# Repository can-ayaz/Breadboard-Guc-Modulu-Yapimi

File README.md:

# Breadboard-Guc-Modulu-Yapimi
**Breadboard Güç Modülü Yapımı**

Breadbord bildiğimiz üzere çok kullanışlı, ve hemen üzerine devre kompanetlerini geçirerek devre kurabileceğimiz bir platform. Tabi bu devreler beslemeye ihtiyaç duyuyorlar, bunun üzerine hazır satılan modüller var ama ben kendim tasarlayarak yapmak istedim.

Daha Fazlası için; https://canayazblog.wordpress.com/2018/06/22/arduino-otto-robot-yapimi/

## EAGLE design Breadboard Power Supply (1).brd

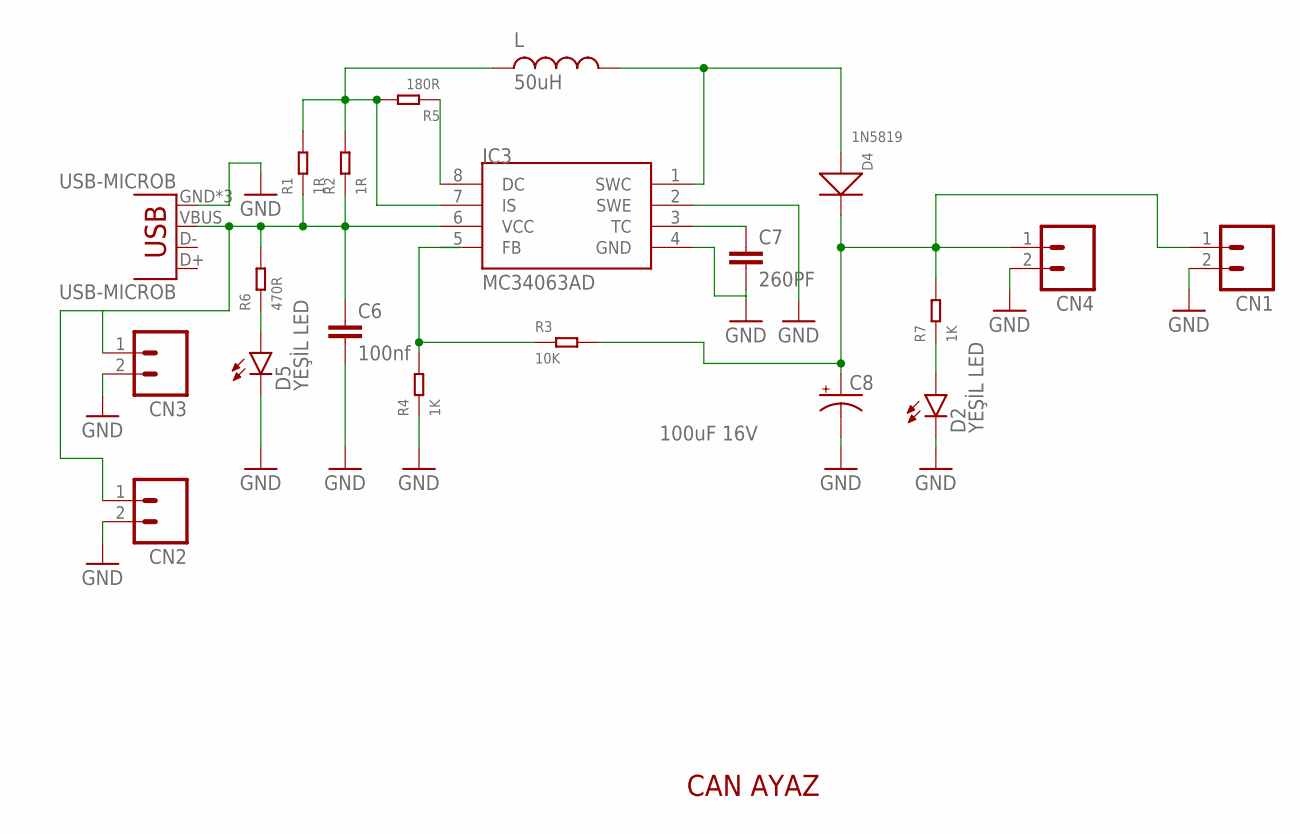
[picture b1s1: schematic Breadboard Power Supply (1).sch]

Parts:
C6: 100nf; 1206
C7: 260PF; 1206
C8: 100uF 16V; PANASONIC_G
CN1, CN2, CN3, CN4: M02; 02P
D2, D5: YEŞİL LED; LED-1206
D4: 1N5819; DO-214AC
IC3: MC34063AD; SOIC8
L: 50uH; MSS1260
R1, R2: 1R; R1206
R3: 10K; R1206
R4, R7: 1K; R1206
R5: 180R; R1206
R6: 470R; R1206
USB-MICROB: USB-MICROB

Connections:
GND: C6.2, C7.2, C8.-, CN1.2, CN2.2, CN3.2, CN4.2, D2.C, D5.C, IC3.2 (SWE), IC3.4 (GND), R4.1, USB-MICROB.GND, USB-MICROB.MT1 (GND), USB-MICROB.MT2 (GND)
unnamed: C8.+, CN1.1, CN4.1, D4.2 (-), R3.2, R7.2
unnamed: C6.1, CN2.1, CN3.1, IC3.6 (VCC), R1.1, R2.1, R6.2, USB-MICROB.VBUS
unnamed: IC3.5 (FB), R3.1, R4.2
unnamed: IC3.7 (IS), L.P$2, R1.2, R2.2, R5.2
unnamed: IC3.8 (DC), R5.1
unnamed: D4.1 (+), IC3.1 (SWC), L.P$1
unnamed: C7.1, IC3.3 (TC)
unnamed: D2.A, R7.1
unnamed: D5.A, R6.1

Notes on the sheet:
CAN AYAZ

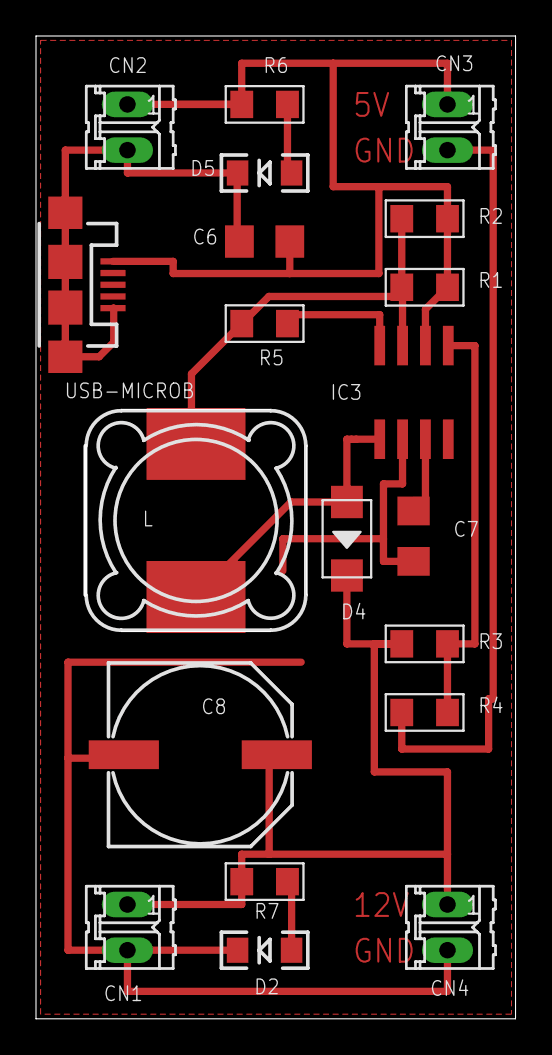
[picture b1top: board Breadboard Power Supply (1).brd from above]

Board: 2 copper layers, 26.4 x 54.4 mm, 20 parts (0 on the bottom side), 10 nets.

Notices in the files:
parts and their libraries:
SparkFun-Connectors: Licensing: Creative Commons ShareAlike 4.0 International - https://creativecommons.org/licenses/by-sa/4.0
